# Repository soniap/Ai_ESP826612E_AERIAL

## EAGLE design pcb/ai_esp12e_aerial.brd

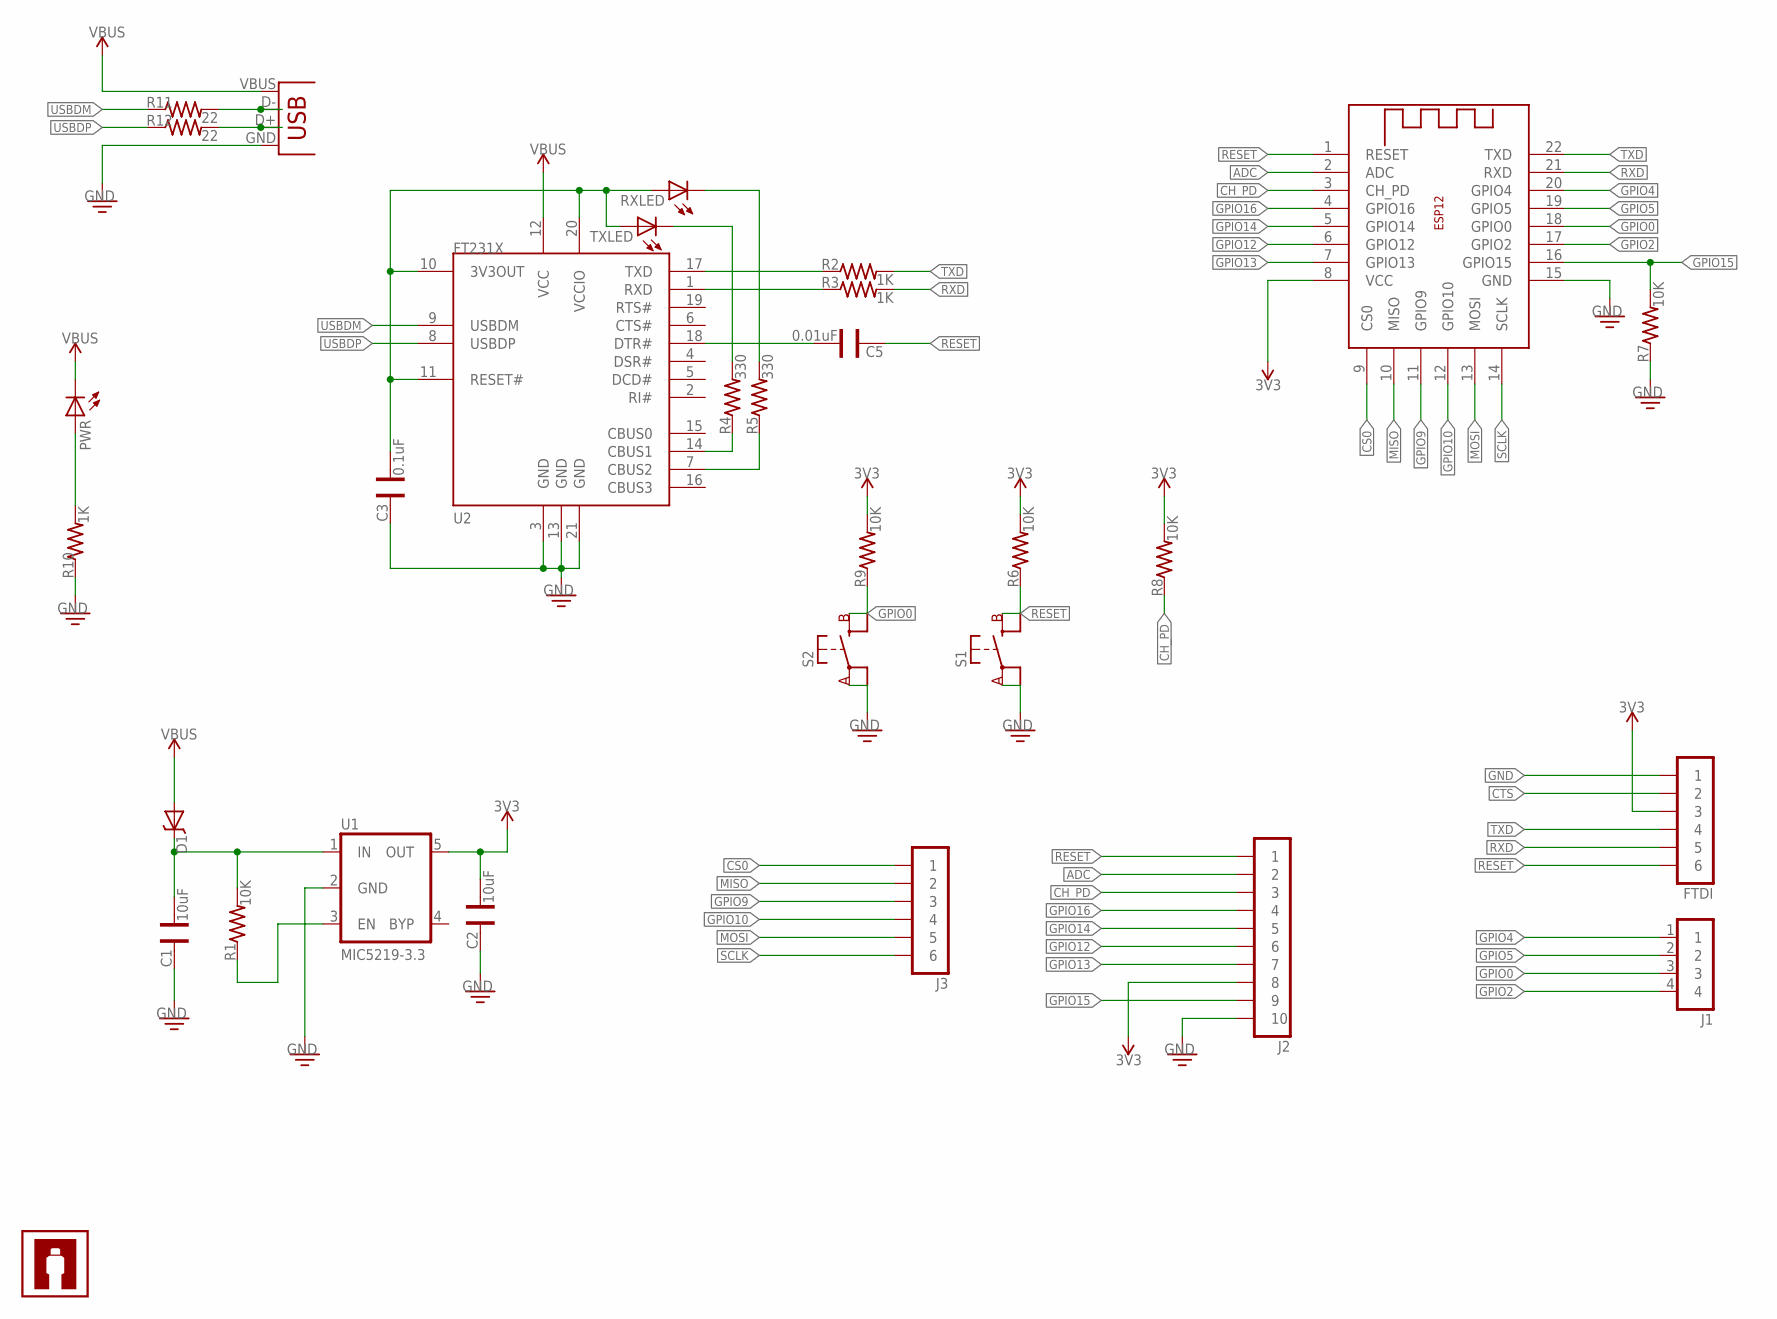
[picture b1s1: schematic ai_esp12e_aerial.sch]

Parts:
C1, C2: 10uF; CAP-0603
C3: 0.1uF; CAP-0603
C5: 0.01uF; CAP-0603
D1: DIODE-SCHOTTKYSOD-523; SOD-523
FTDI: 1X06FTDI; 1X06-CUSTOMSP
J1: 1X04NFNS; 1X04-NFNS
J2: 1X10NFNS; 1X10-NFNS
J3: 1X061X06-NFNS; 1X06-NFNS
PWR: LED0603; LED-0603
R1, R6, R7, R8, R9: 10K; RES-0603
R2, R3, R10: 1K; RES-0603
R4, R5: 330; RES-0603
R11, R12: 22; RES-0603
RXLED: LED0603; LED-0603
S1, S2: SW-SPSTSMD06X035; SW-SPST-SMD06X-035
TXLED: LED0603; LED-0603
U1: MIC5219-3.3; SOT23-5
U2: FT231X-Q; QFN20
U$1: AI-LOGOXS; AI-LOGO-XS
USB1: USBMICROB-TH; USB-MICROB-TH
X1: ESP-12

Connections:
3V3: C2.1, FTDI.3, J2.8, R6.2, R8.2, R9.2, U1.5 (OUT), X1.8 (VCC)
ADC: J2.2, X1.2 (ADC)
CH_PD: J2.3, R8.1, X1.3 (CH_PD)
CS0: J3.1, X1.9 (CS0)
CTS: FTDI.2
GND: C1.2, C2.2, C3.2, FTDI.1, J2.10, R7.1, R10.1, S1.P$1 (A), S2.P$1 (A), U1.2 (GND), U2.3 (GND), U2.13 (GND), U2.21 (GND), USB1.GND, X1.15 (GND)
GPIO0: J1.3, R9.1, S2.P$2 (B), X1.18 (GPIO0)
GPIO2: J1.4, X1.17 (GPIO2)
GPIO4: J1.1, X1.20 (GPIO4)
GPIO5: J1.2, X1.19 (GPIO5)
GPIO9: J3.3, X1.11 (GPIO9)
GPIO10: J3.4, X1.12 (GPIO10)
GPIO12: J2.6, X1.6 (GPIO12)
GPIO13: J2.7, X1.7 (GPIO13)
GPIO14: J2.5, X1.5 (GPIO14)
GPIO15: J2.9, R7.2, X1.16 (GPIO15)
GPIO16: J2.4, X1.4 (GPIO16)
MISO: J3.2, X1.10 (MISO)
MOSI: J3.5, X1.13 (MOSI)
unnamed: C1.1, D1.C, R1.2, U1.1 (IN)
unnamed: R2.1, U2.17 (TXD)
unnamed: R1.1, U1.3 (EN)
unnamed: C3.1, RXLED.A, TXLED.A, U2.10 (3V3OUT), U2.11 (RESET#), U2.20 (VCCIO)
unnamed: R3.1, U2.1 (RXD)
unnamed: R4.2, TXLED.C
unnamed: R5.1, U2.7 (CBUS2)
unnamed: R4.1, U2.14 (CBUS1)
unnamed: R5.2, RXLED.C
unnamed: C5.1, U2.18 (DTR#)
unnamed: PWR.A, R10.2
unnamed: R11.2, USB1.D-
unnamed: R12.2, USB1.D+
RESET: C5.2, FTDI.6, J2.1, R6.1, S1.P$2 (B), X1.1 (RESET)
RXD: FTDI.5, R3.2, X1.21 (RXD)
SCLK: J3.6, X1.14 (SCLK)
TXD: FTDI.4, R2.2, X1.22 (TXD)
USBDM: R11.1, U2.9 (USBDM)
USBDP: R12.1, U2.8 (USBDP)
VBUS: D1.A, PWR.C, U2.12 (VCC), USB1.VBUS

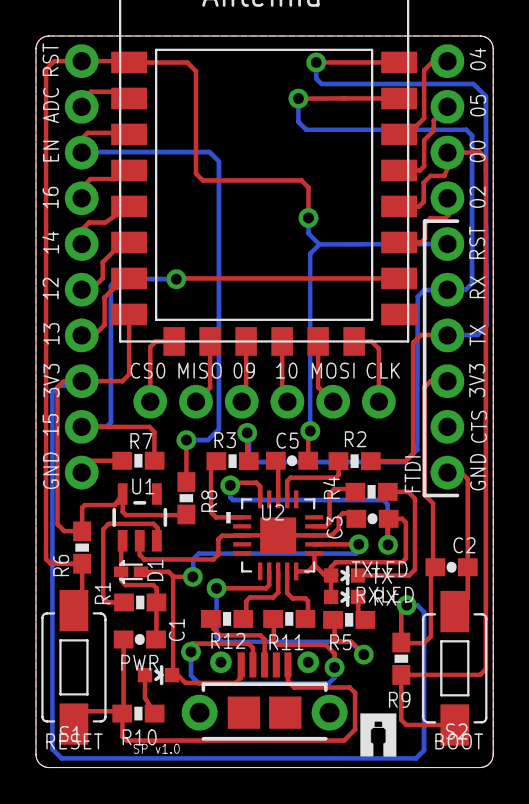
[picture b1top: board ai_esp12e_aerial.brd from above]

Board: 2 copper layers, 25.4 x 40.6 mm, 31 parts (0 on the bottom side), 38 nets.

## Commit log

2015-08-18 updated board
2015-08-19 update on board
2015-10-13 Delete ai_esp12e_iotag.sch
    Duplicate - wrong repo.
2015-10-13 Delete ai_esp12e_iotag.brd
    Duplicate- wrong repo.
